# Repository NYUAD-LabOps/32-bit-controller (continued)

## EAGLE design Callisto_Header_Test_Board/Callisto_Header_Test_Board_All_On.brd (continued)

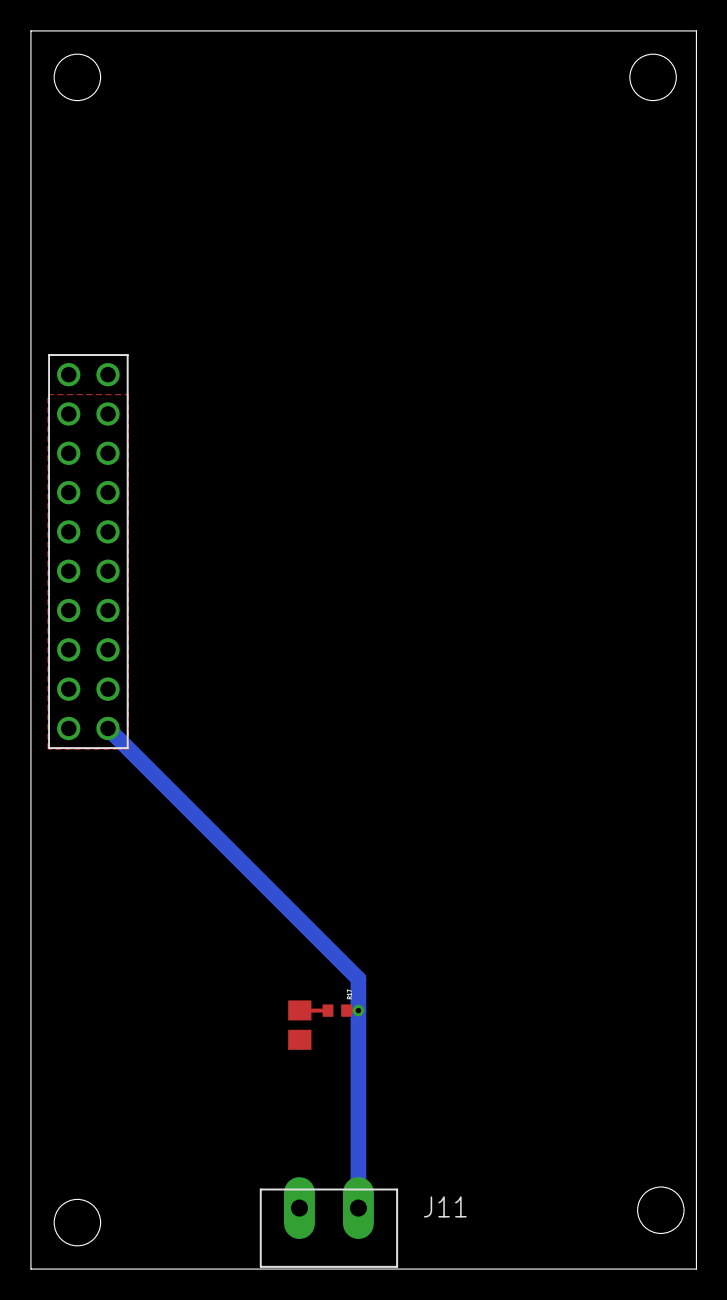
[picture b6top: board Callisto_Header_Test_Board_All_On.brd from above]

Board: 2 copper layers, 43.0 x 80.0 mm, 4 parts (0 on the bottom side), 3 nets.
